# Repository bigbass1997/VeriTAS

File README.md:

### Description
VeriTAS is a combination of a replay device for performing Tool-Assisted-Speedruns (aka Tool-Assisted-Superruns) on physical hardware, and software tooling that interfaces with the device and assists in other TAS replay tasks.

The RP2040 microcontroller is the brains of this device. This project is still in development, and is a replacement/continuation of my previous device, the PICTAS. It is _not_ yet ready for wide-spread public use.

### Software Tooling
The [VeriTAS software](veritas-cli/) is a CLI tool that can perform various TAS replay related tasks, such as automated TAS dumping and video transcoding. It is also used for interfacing with the VeriTAS hardware.

### Input Displays
_Planned_

### Discord/Support
If you have questions or suggestions, you can find me on the [TASBot Labs](https://discord.tas.bot/) or [TASVideos](https://discord.gg/7KSr7eZVzG) Discord servers.

### Licensing
The `/veritas-hardware/` directory is licensed under CERN-OHL-W-V2, while all other files are dual licensed under MIT and APACHE 2.0.

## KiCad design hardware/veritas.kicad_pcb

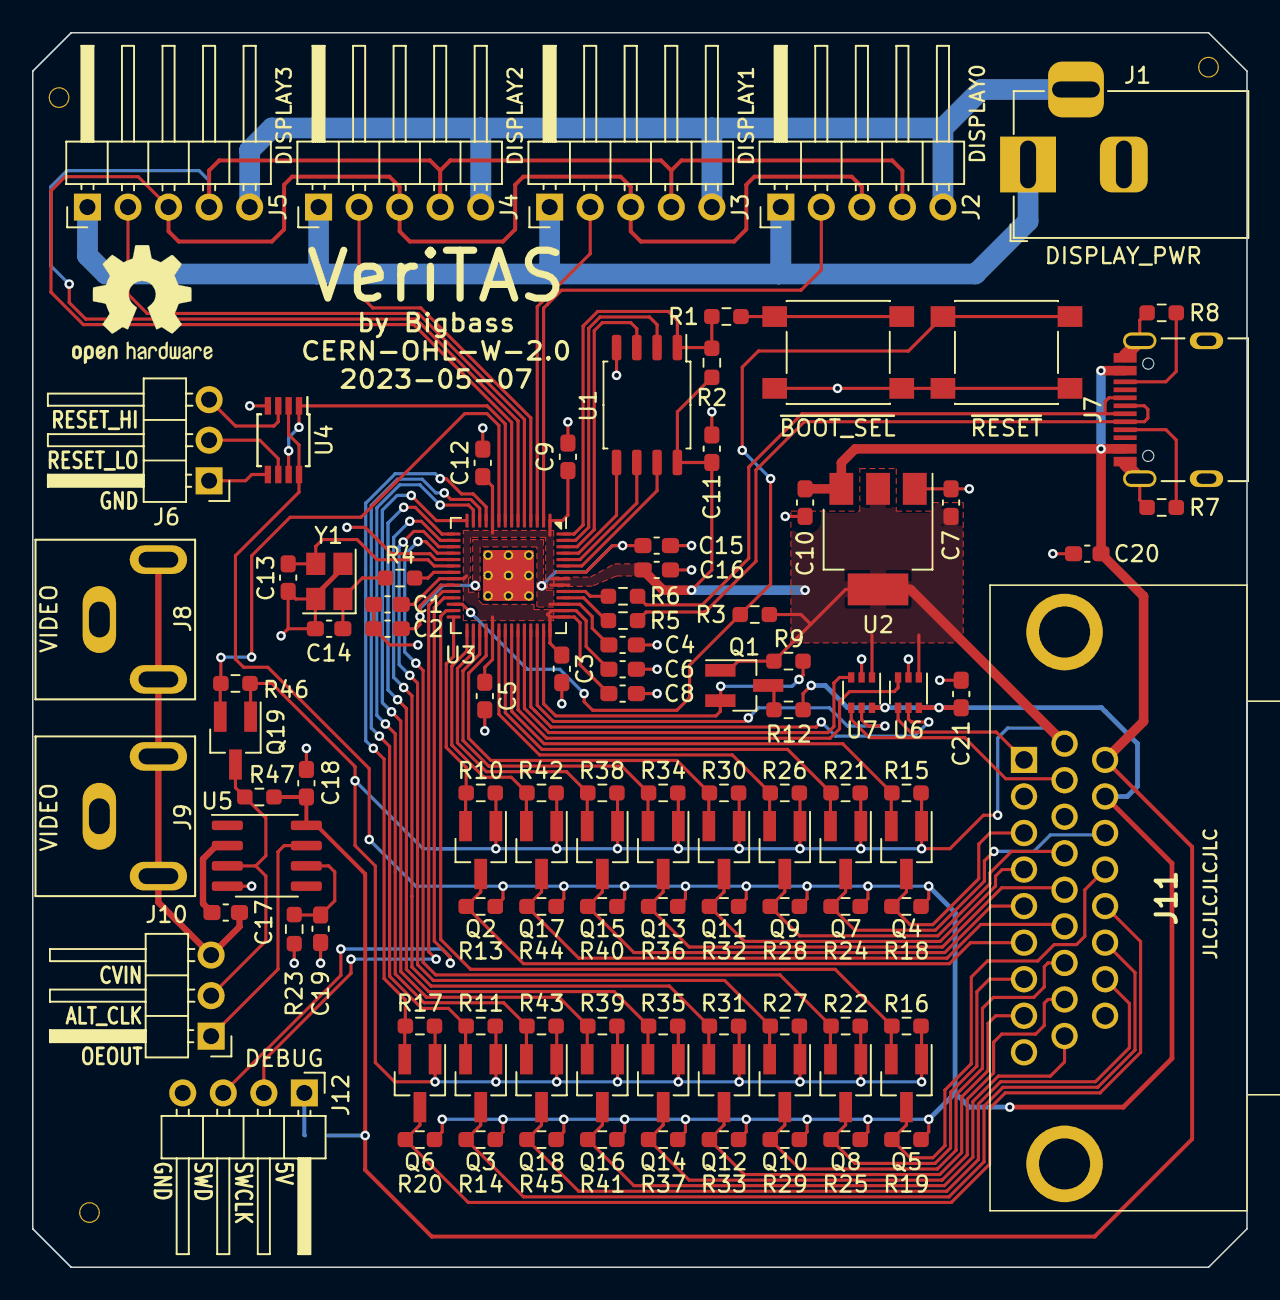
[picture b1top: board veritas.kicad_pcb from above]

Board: 2 copper layers, 76.1 x 77.3 mm, 110 parts (1 on the bottom side), 83 nets.

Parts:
C1, C2, C3, C4, C5, C6, C8, C9, C11, C12, C17, C18, C19, C20, C21: 0.1uF; C_0603_1608Metric_Pad1.08x0.95mm_HandSolder
C7, C10: 10uF; C_0603_1608Metric_Pad1.08x0.95mm_HandSolder
C13, C14: 27pF; C_0603_1608Metric_Pad1.08x0.95mm_HandSolder
C15, C16: 1uF; C_0603_1608Metric_Pad1.08x0.95mm_HandSolder
J1: DISPLAY_PWR; BarrelJack_Horizontal
J2: DISPLAY0; PinHeader_1x05_P2.54mm_Horizontal
J3: DISPLAY1; PinHeader_1x05_P2.54mm_Horizontal
J4: DISPLAY2; PinHeader_1x05_P2.54mm_Horizontal
J5: DISPLAY3; PinHeader_1x05_P2.54mm_Horizontal
J6: CON_RESET; PinHeader_1x03_P2.54mm_Horizontal
J7: USB2.0_C; TYPE-C-31-M-12
J8, J9: VIDEO; PJRAN1X1U04X
J10: SYNC; PinHeader_1x03_P2.54mm_Horizontal
J11: CONTROLLER_PORT; L77HDA26SD1CH4R
J12: DEBUG; PinHeader_1x04_P2.54mm_Horizontal
JP1: SolderJumper_2_Open; SolderJumper-2_P1.3mm_Open_TrianglePad1.0x1.5mm
Q1, Q2, Q3, Q4, Q5, Q6, Q7, Q8, Q9, Q10, Q11, Q12, Q13, Q14, Q15, Q16, Q17, Q18, Q19: 2N7002K; SOT-23_Handsoldering
R1, R4: 1K; R_0603_1608Metric_Pad0.98x0.95mm_HandSolder
R2, R3, R9, R10, R11, R12, R13, R14, R15, R16, R17, R18, R19, R20, R21, R22, R24, R25, R26, R27, R28, R29, R30, R31, R32, R33, R34, R35, R36, R37, R38, R39, R40, R41, R42, R43, R44, R45, R46, R47: 10K; R_0603_1608Metric_Pad0.98x0.95mm_HandSolder
R5, R6: 27; R_0603_1608Metric_Pad0.98x0.95mm_HandSolder
R7, R8: 5.1K; R_0603_1608Metric_Pad0.98x0.95mm_HandSolder
R23: 680K; R_0603_1608Metric_Pad0.98x0.95mm_HandSolder
SW1: ~{BOOT_SEL}; SW_SPST_PTS645
SW2: ~{RESET}; SW_SPST_PTS645
U1: W25Q128JVSIQ; SOIC-8_5.23x5.23mm_P1.27mm
U2: NCP1117ST33T3G; SOT-223-3_TabPin2
U3: RP2040
U4: 74LVC2G240; TSSOP-8_3x3mm_P0.65mm
U5: LM1881; SOIC-8_3.9x4.9mm_P1.27mm
U6, U7: SN74LVC1T45DRL; SOT-363_SC-70-6
Y1: 12MHz; Crystal_SMD_3225-4Pin_3.2x2.5mm

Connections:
+1V1: C2.1, C4.1, C15.2, U3.23 (DVDD), U3.45 (VREG_VOUT), U3.50 (DVDD)
+3V3: C1.1, C3.1, C5.1, C6.1, C7.1, C8.1, C9.1, C11.1, C12.1, C16.2, J11.10, Q1.1 (G), Q2.1 (G), Q3.1 (G), Q4.1 (G), Q5.1 (G), Q6.1 (G), Q7.1 (G), Q8.1 (G), Q9.1 (G), Q10.1 (G), Q11.1 (G), Q12.1 (G), Q13.1 (G), Q14.1 (G), Q15.1 (G), Q16.1 (G), Q17.1 (G), Q18.1 (G), Q19.1 (G), R2.2, R3.2, R9.2, R10.2, R11.2, R15.2, R16.2, R17.2, R21.2, R22.2, R26.2, R27.2, R30.2, R31.2, R34.2, R35.2, R38.2, R39.2, R42.2, R43.2, R46.2, U1.8 (VCC), U2.2 (VO), U3.1 (IOVDD), U3.10 (IOVDD), U3.22 (IOVDD), U3.33 (IOVDD), U3.42 (IOVDD), U3.43 (ADC_AVDD), U3.44 (VREG_IN), U3.48 (USB_VDD), U3.49 (IOVDD), U6.1 (VCCA), U7.1 (VCCA)
/CVIN: C17.2, J8.1 (In), J9.1 (In), J10.3
/D+: J7.A6 (D+), J7.B6 (D+), R6.2
/D-: J7.A7 (D-), J7.B7 (D-), R5.2
/LED_5V: J1.1, J2.1, J3.1, J4.1, J5.1
/RD+: R6.1, U3.47 (USB_DP)
/RD-: R5.1, U3.46 (USB_DM)
/RESET_HI: J6.3, U4.3 (2Y)
/RESET_LO: J6.2, U4.6 (1Y)
ALT_CLK_A: Q19.2 (S), R46.1, U3.9 (GPIO7)
ALT_CLK_B: J10.2, Q19.3 (D), R47.1, U5.3 (VSOUT)
CNT_0: Q6.2 (S), R17.1, U3.11 (GPIO8)
CNT_1: Q3.2 (S), R11.1, U3.12 (GPIO9)
CNT_2: Q18.2 (S), R43.1, U3.13 (GPIO10)
CNT_3: Q16.2 (S), R39.1, U3.14 (GPIO11)
CNT_4: Q14.2 (S), R35.1, U3.15 (GPIO12)
CNT_5: Q12.2 (S), R31.1, U3.16 (GPIO13)
CNT_6: Q10.2 (S), R27.1, U3.17 (GPIO14)
CNT_7: Q8.2 (S), R22.1, U3.18 (GPIO15)
CNT_8: Q5.2 (S), R16.1, U3.27 (GPIO16)
CNT_9: Q2.2 (S), R10.1, U3.28 (GPIO17)
CNT_10: Q17.2 (S), R42.1, U3.29 (GPIO18)
CNT_11: Q15.2 (S), R38.1, U3.30 (GPIO19)
CNT_12: Q13.2 (S), R34.1, U3.31 (GPIO20)
CNT_13: Q11.2 (S), R30.1, U3.32 (GPIO21)
CNT_14: Q9.2 (S), R26.1, U3.34 (GPIO22)
CNT_15: Q7.2 (S), R21.1, U3.35 (GPIO23)
CNT_16: Q4.2 (S), R15.1, U3.36 (GPIO24)
CNT_17: U3.37 (GPIO25), U6.3 (A)
CNT_17_DIR: U3.39 (GPIO27_ADC1), U6.5 (DIR)
CNT_18: U3.38 (GPIO26_ADC0), U7.3 (A)
CNT_18_DIR: U3.40 (GPIO28_ADC2), U7.5 (DIR)
CP_1: J11.1, U6.4 (B)
CP_3: J11.3, Q4.3 (D), R18.1
CP_4: J11.4, Q11.3 (D), R32.1
CP_5: J11.5, Q15.3 (D), R40.1
CP_6: J11.6, Q2.3 (D), R13.1
CP_7: J11.7, Q8.3 (D), R25.1
CP_8: J11.8, Q12.3 (D), R33.1
CP_11: J11.11, U7.4 (B)
CP_13: J11.13, Q9.3 (D), R28.1
CP_14: J11.14, Q13.3 (D), R36.1
CP_15: J11.15, Q17.3 (D), R44.1
CP_16: J11.16, Q10.3 (D), R29.1
CP_17: J11.17, Q14.3 (D), R37.1
CP_18: J11.18, Q16.3 (D), R41.1
CP_21: J11.21, Q7.3 (D), R24.1
CP_22: J11.22, Q5.3 (D), R19.1
CP_23: J11.23, Q6.3 (D), R20.1
CP_24: J11.24, Q3.3 (D), R14.1
CP_25: J11.25, Q18.3 (D), R45.1
DETECT: Q1.2 (S), R9.1, U3.41 (GPIO29_ADC3)
DISPLAY_CLK: J2.3, J3.3, J4.3, J5.3, U3.7 (GPIO5)
DISPLAY_SER: J2.4, J3.4, J4.4, J5.4, U3.6 (GPIO4)
DISPLAY_STROBE0: J2.2, U3.2 (GPIO0)
DISPLAY_STROBE1: J3.2, U3.3 (GPIO1)
DISPLAY_STROBE2: J4.2, U3.4 (GPIO2)
DISPLAY_STROBE3: J5.2, U3.5 (GPIO3)
GND: C1.2, C2.2, C3.2, C4.2, C5.2, C6.2, C7.2, C8.2, C9.2, C10.2, C11.2, C12.2, C13.1, C14.1, C15.1, C16.1, C18.1, C19.1, C20.2, C21.2, J1.2, J1.3, J2.5, J3.5, J4.5, J5.5, J6.1, J7.A1 (GND), J7.A12 (GND), J7.B1 (GND), J7.B12 (GND), J7.S1 (SHIELD), J8.2 (Ext), J9.2 (Ext), J11.0, J11.9, J11.26, J12.4, R7.1, R8.1, R23.2, SW1.1, SW2.1, U1.4 (GND), U2.1 (GND), U3.19 (TESTEN), U3.57 (GND), U4.4 (GND), U4.5 (2A), U5.4 (GND), U6.2 (GND), U7.2 (GND), Y1.2, Y1.4
unnamed: C14.2, R4.1, Y1.1
unnamed: J7.A5 (CC1), R7.2
unnamed: J7.B5 (CC2), R8.2
unnamed: J12.1, JP1.2 (B)
unnamed: Q1.3 (D), R12.1
unnamed: R1.1, SW1.2
unnamed: R3.1, SW2.2, U3.26 (RUN)
unnamed: C13.2, U3.20 (XIN), Y1.3
unnamed: R4.2, U3.21 (XOUT)
unnamed: C17.1, U5.2 (CVIN)
unnamed: C19.2, R23.1, U5.6 (RSET)
OEOUT: J10.1, U5.7 (OEOUT)
QSPI_CLK: U1.6 (CLK), U3.52 (QSPI_SCLK)
QSPI_IO0: U1.5 (DI(IO0)), U3.53 (QSPI_SD0)
QSPI_IO1: U1.2 (DO(IO1)), U3.55 (QSPI_SD1)
QSPI_IO2: U1.3 (IO2), U3.54 (QSPI_SD2)
QSPI_IO3: U1.7 (IO3), U3.51 (QSPI_SD3)
SWCLK: J12.2, U3.24 (SWCLK)
SWD: J12.3, U3.25 (SWD)
SYSTEM_PWR: C21.1, J11.20, R12.2, R13.2, R14.2, R18.2, R19.2, R20.2, R24.2, R25.2, R28.2, R29.2, R32.2, R33.2, R36.2, R37.2, R40.2, R41.2, R44.2, R45.2, U4.2 (1A), U4.8 (VCC), U6.6 (VCCB), U7.6 (VCCB)
VBUS: C10.1, C18.2, C20.1, J7.A4 (VBUS), J7.A9 (VBUS), J7.B4 (VBUS), J7.B9 (VBUS), J11.19, JP1.1 (A), R47.2, U2.3 (VI), U5.8 (VCC)
~CON_RESET: U3.8 (GPIO6), U4.1 (1~OE), U4.7 (2~OE)
~QSPI_CS: R1.2, R2.1, U1.1 (~CS), U3.56 (QSPI_SS)

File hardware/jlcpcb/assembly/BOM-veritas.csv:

Comment,Designator,Footprint,LCSC
27pF,"C13,C14",C_0603_1608Metric_Pad1.08x0.95mm_HandSolder,C107045
LMBT3946DW1T1G,Q1,SOT-363_SC-70-6_Handsoldering,C136169
0.1uF,"C1,C11,C12,C17,C18,C19,C2,C20,C21,C3,C4,C5,C6,C8,C9",C_0603_1608Metric_Pad1.08x0.95mm_HandSolder,C14663
1uF,"C15,C16",C_0603_1608Metric_Pad1.08x0.95mm_HandSolder,C15849
USB2.0_C,J7,TYPE-C-31-M-12,C165948
RP2040,U3,RP2040,C2040
1K,"R1,R3",R_0603_1608Metric_Pad0.98x0.95mm_HandSolder,C21190
~{BOOT_SEL},SW1,SW_SPST_PTS645,C221875
5.1K,"R6,R7",R_0603_1608Metric_Pad0.98x0.95mm_HandSolder,C23186
27,"R4,R5",R_0603_1608Metric_Pad0.98x0.95mm_HandSolder,C25190
10K,"R10,R11,R12,R13,R14,R15,R16,R17,R18,R19,R2,R20,R21,R23,R24,R25,R26,R27,R28,R29,R30,R31,R32,R33,R34,R35,R36,R37,R38,R39,R40,R41,R42,R43,R44,R45,R46,R8,R9",R_0603_1608Metric_Pad0.98x0.95mm_HandSolder,C25804
680K,R22,R_0603_1608Metric_Pad0.98x0.95mm_HandSolder,C25822
NCP1117ST33T3G,U2,SOT-223-3_TabPin2,C26537
12MHz,Y1,Crystal_SMD_HC49-SD,C326543
2N7002K,"Q10,Q11,Q12,Q13,Q14,Q15,Q16,Q17,Q18,Q19,Q2,Q20,Q3,Q4,Q5,Q6,Q7,Q8,Q9",SOT-23_Handsoldering,C8545
SN74LVC1T45DRL,"U5,U6",SOT-563,C9382
10uF,"C10,C7",C_0603_1608Metric_Pad1.08x0.95mm_HandSolder,C96446
W25Q128JVSIQ,U1,SOIC-8_5.23x5.23mm_P1.27mm,C97521
DISPLAY3,J5,PinHeader_1x05_P2.54mm_Horizontal,
SYNC,J10,PinHeader_1x03_P2.54mm_Horizontal,
VIDEO,J9,PJRAN1X1U04X,
DISPLAY0,J2,PinHeader_1x05_P2.54mm_Horizontal,
DEBUG,J12,PinHeader_1x04_P2.54mm_Horizontal,
VIDEO,J8,PJRAN1X1U04X,
LM1881,U4,SOIC-8_3.9x4.9mm_P1.27mm,
DISPLAY2,J4,PinHeader_1x05_P2.54mm_Horizontal,
CON_RESET,J6,PinHeader_1x03_P2.54mm_Horizontal,
DISPLAY1,J3,PinHeader_1x05_P2.54mm_Horizontal,
DISPLAY_PWR,J1,BarrelJack_Horizontal,
CONTROLLER_PORT,J11,L77HDA26SD1CH4R,

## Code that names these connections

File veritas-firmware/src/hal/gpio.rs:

#![allow(unused)]

use rp2040_pac::{IO_BANK0, PADS_BANK0, SIO};
use rp2040_pac::io_bank0::gpio::gpio_ctrl::{FUNCSEL_A, FUNCSEL_R};
use rp2040_pac::pads_bank0::gpio::{DRIVE_A, DRIVE_R};

pub const PIN_DISPLAY_STROBE0: Gpio = Gpio(0);
pub const PIN_DISPLAY_STROBE1: Gpio = Gpio(1);
pub const PIN_DISPLAY_STROBE2: Gpio = Gpio(2);
pub const PIN_DISPLAY_STROBE3: Gpio = Gpio(3);
pub const PIN_DISPLAY_SER: Gpio = Gpio(4);
pub const PIN_DISPLAY_CLK: Gpio = Gpio(5);

pub const PIN_CON_RESET: Gpio = Gpio(6);
pub const PIN_ALT_CLK: Gpio = Gpio(7);

pub const PIN_CNT_0: Gpio = Gpio(8);
pub const PIN_CNT_1: Gpio = Gpio(9);
pub const PIN_CNT_2: Gpio = Gpio(10);
pub const PIN_CNT_3: Gpio = Gpio(11);
pub const PIN_CNT_4: Gpio = Gpio(12);
pub const PIN_CNT_5: Gpio = Gpio(13);
pub const PIN_CNT_6: Gpio = Gpio(14);
pub const PIN_CNT_7: Gpio = Gpio(15);
pub const PIN_CNT_8: Gpio = Gpio(16);
pub const PIN_CNT_9: Gpio = Gpio(17);
pub const PIN_CNT_10: Gpio = Gpio(18);
pub const PIN_CNT_11: Gpio = Gpio(19);
pub const PIN_CNT_12: Gpio = Gpio(20);
pub const PIN_CNT_13: Gpio = Gpio(21);
pub const PIN_CNT_14: Gpio = Gpio(22);
pub const PIN_CNT_15: Gpio = Gpio(23);
pub const PIN_CNT_16: Gpio = Gpio(24);

pub const PIN_CNT_17: Gpio = Gpio(25);
pub const PIN_CNT_18: Gpio = Gpio(26);
pub const PIN_CNT_17_DIR: Gpio = Gpio(27);
pub const PIN_CNT_18_DIR: Gpio = Gpio(28);

pub const PIN_DETECT: Gpio = Gpio(29);

pub const CP_1: Gpio = PIN_CNT_17;
pub const CP_1_DIR: Gpio = PIN_CNT_17_DIR;

//pub const CP_2: Gpio = PIN_CNT_; // Unconnected
pub const CP_3: Gpio = PIN_CNT_16;
pub const CP_4: Gpio = PIN_CNT_13;
pub const CP_5: Gpio = PIN_CNT_11;
pub const CP_6: Gpio = PIN_CNT_9;
pub const CP_7: Gpio = PIN_CNT_7;
pub const CP_8: Gpio = PIN_CNT_5;

pub const CP_11: Gpio = PIN_CNT_18;
pub const CP_11_DIR: Gpio = PIN_CNT_18_DIR;

//pub const CP_12: Gpio = PIN_CNT_; // Unconnected
pub const CP_13: Gpio = PIN_CNT_14;
pub const CP_14: Gpio = PIN_CNT_12;
pub const CP_15: Gpio = PIN_CNT_10;
pub const CP_16: Gpio = PIN_CNT_6;
pub const CP_17: Gpio = PIN_CNT_4;
pub const CP_18: Gpio = PIN_CNT_3;

pub const CP_21: Gpio = PIN_CNT_15;
pub const CP_22: Gpio = PIN_CNT_8;
pub const CP_23: Gpio = PIN_CNT_0;
pub const CP_24: Gpio = PIN_CNT_1;
pub const CP_25: Gpio = PIN_CNT_2;

#[derive(Debug, Clone, Copy, PartialEq, Eq)]
pub struct Gpio(pub usize);
impl Gpio {
    pub const fn new(gpio: usize) -> Self {
        Self(gpio)
    }
    
    #[inline(always)]
    pub fn function(self) -> FUNCSEL_R {
        unsafe { (*IO_BANK0::ptr()).gpio(self.0).gpio_ctrl().read().funcsel() }
    }
    
    #[inline(always)]
    pub fn set_function(self, func: FUNCSEL_A) -> Self {
        unsafe {
            (*IO_BANK0::ptr()).gpio(self.0).gpio_ctrl().write_with_zero(|w| w.funcsel().variant(func));
            self.set_output_disable(false);
        }
        
        self
    }
    
    #[inline(always)]
    pub fn output_disable(self) -> bool {
        unsafe { (*PADS_BANK0::ptr()).gpio(self.0).read().od().bit() }
    }
    
    #[inline(always)]
    pub fn set_output_disable(self, od: bool) -> Self {
        unsafe { (*PADS_BANK0::ptr()).gpio(self.0).modify(|_, w| w.od().bit(od)); }
        
        self
    }
    
    #[inline(always)]
    pub fn input_enable(self) -> bool {
        unsafe {
            (*PADS_BANK0::ptr()).gpio(self.0).read().ie().bit()
        }
    }
    
    #[inline(always)]
    pub fn set_input_enable(self, ie: bool) -> Self {
        unsafe { (*PADS_BANK0::ptr()).gpio(self.0).modify(|_, w| w.ie().bit(ie)); }
        
        self
    }
    
    /// Returns the state of this GPIO's SIO output enable.
    /// 
    /// Note: This setting should have no effect if the GPIO's function is _not_ set to SIO. 
    #[inline(always)]
    pub fn output_enable(self) -> bool {
        unsafe {
            (*SIO::ptr()).gpio_oe().read().bits() & (1 << self.0) != 0
        }
    }
    
    /// Configures this GPIO's SIO output enable.
    /// 
    /// Note: This setting should have no effect if the GPIO's function is _not_ set to SIO. 
    #[inline(always)]
    pub fn set_sio_output_enable(self, oe: bool) -> Self {
        unsafe {
            if oe {
                (*SIO::ptr()).gpio_oe_set().write(|w| w.bits(1 << self.0));
            } else {
                (*SIO::ptr()).gpio_oe_clr().write(|w| w.bits(1 << self.0));
            }
        }
        
        self
    }
    
    #[inline(always)]
    pub fn drive(self) -> DRIVE_R {
        unsafe { (*PADS_BANK0::ptr()).gpio(self.0).read().drive() }
    }
    
    #[inline(always)]
    pub fn set_drive(self, drive: DRIVE_A) -> Self {
        unsafe { (*PADS_BANK0::ptr()).gpio(self.0).modify(|_, w| w.drive().variant(drive)); }
        
        self
    }
    
    #[inline(always)]
    pub fn pull_up_enable(self) -> bool {
        unsafe { (*PADS_BANK0::ptr()).gpio(self.0).read().pue().bit() }
    }
    
    #[inline(always)]
    pub fn set_pull_up_enable(self, pue: bool) -> Self {
        unsafe { (*PADS_BANK0::ptr()).gpio(self.0).modify(|_, w| w.pue().bit(pue)); }
        
        self
    }
    
    #[inline(always)]
    pub fn pull_down_enable(self) -> bool {
        unsafe { (*PADS_BANK0::ptr()).gpio(self.0).read().pde().bit() }
    }
    
    #[inline(always)]
    pub fn set_pull_down_enable(self, pde: bool) -> Self {
        unsafe { (*PADS_BANK0::ptr()).gpio(self.0).modify(|_, w| w.pde().bit(pde)); }
        
        self
    }
    
    #[inline(always)]
    pub fn schmitt_enable(self) -> bool {
        unsafe { (*PADS_BANK0::ptr()).gpio(self.0).read().schmitt().bit() }
    }
    
    #[inline(always)]
    pub fn set_schmitt_enable(self, schmitt: bool) -> Self {
        unsafe { (*PADS_BANK0::ptr()).gpio(self.0).modify(|_, w| w.schmitt().bit(schmitt)); }
        
        self
    }
    
    #[inline(always)]
    pub fn slewrate(self) -> bool {
        unsafe { (*PADS_BANK0::ptr()).gpio(self.0).read().slewfast().bit() }
    }
    
    #[inline(always)]
    pub fn set_slewrate(self, is_fast: bool) -> Self {
        unsafe { (*PADS_BANK0::ptr()).gpio(self.0).modify(|_, w| w.slewfast().bit(is_fast)); }
        
        self
    }
    
    #[inline(always)]
    pub fn is_high(self) -> bool {
        unsafe {
            (*SIO::ptr()).gpio_in().read().bits() & (1 << self.0) != 0
        }
    }
    
    #[inline(always)]
    pub fn is_low(self) -> bool {
        unsafe {
            (*SIO::ptr()).gpio_in().read().bits() & (1 << self.0) == 0
        }
    }
    
    #[inline(always)]
    pub fn set_high(self) -> Self {
        unsafe {
            (*SIO::ptr()).gpio_out_set().write(|w| w.bits(1 << self.0));
        }
        
        self
    }
    
    #[inline(always)]
    pub fn set_low(self) -> Self {
        unsafe {
            (*SIO::ptr()).gpio_out_clr().write(|w| w.bits(1 << self.0));
        }
        
        self
    }
    
    #[inline(always)]
    pub fn into_input(self, pull_up: bool, pull_down: bool) -> Self {
        self.set_function(FUNCSEL_A::SIO);
        self.set_pull_down_enable(pull_down);
        self.set_pull_up_enable(pull_up);
        self.set_output_disable(true);
        self.set_input_enable(true);
        self.set_sio_output_enable(false);
        
        self
    }
    
    #[inline(always)]
    pub fn into_output(self, pull_up: bool, pull_down: bool) -> Self {
        self.set_function(FUNCSEL_A::SIO);
        self.set_pull_down_enable(pull_down);
        self.set_pull_up_enable(pull_up);
        self.set_output_disable(false);
        self.set_input_enable(false);
        self.set_sio_output_enable(true);
        
        self
    }
}

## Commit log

2022-07-16 Initial commit.
2022-07-17 Reworked dumping data into well-defined structs. Still need logic for movies to fetch their expected rom hash.
2022-07-18 Implemented rom searching and interfacing with FCEUX. Bizhawk is next..
2022-07-19 Added warnings for unsupported movie formats and for invalid Pub/Sub IDs.
2022-07-19 Implemented Bizhawk interfacing.
2022-07-20 Fixed clap bug for encode command.
2022-07-20 Added dump file location to log output.
2022-08-08 Partially migrate away from using the restrictive RP2040-HAL, and more toward a custom HAL using the RP2040-PAC.
2022-08-09 Implemented basic N64 replay functionality (temporary host API), and GPIO functions.
2022-08-10 Cleaned and reorganized code some.
2022-08-11 Added global allocator, and started on storing auxiliary data storage (e.g. transitions).
2022-08-11 Migrate software into project tree.
2022-08-11 Remove duplicated files caused by history merge.
2022-08-11 Updated READMEs and added license notice.
2022-08-12 Fixed significant issues with custom GPIO functions, and started on NES replay.
2022-08-12 Stop using board-specific rp-pico dependency. Fix imports accordingly.
2022-08-12 Setup separate, mutable, Interrupt Vector Tables for each core.
2022-08-12 Hopefully fixed remaining GPIO issues.
2022-08-12 1-player NES replay is functional.
2022-08-14 Implemented 2-player NES replay.
2022-08-24 Finished first hardware prototype.
2022-08-26 Ignore ibom.
2022-08-27 Started organizing host<->device communication protocol.
2022-08-27 Added partial protocol documentation to README.
2022-08-27 Update lua scripts to use latest dev version of TASD spec.
2022-08-27 Implemented structured replay device communication protocol.
2022-08-27 Included system byte in ProvideInput command response.
2022-08-27 Fixed TASD API bug, and added transition debug messages to Bizhawk script.
2022-09-06 Improved ProvideInput communication and added manual control for NES.
2022-09-06 Changed from UART to USB communication. Changed NES pinout for testing. Added gpio pin consts which reflect PCB pinout.
2022-09-06 Completed new PCB revision. Includes different voltage translation and removal of unnecessary parts.
2022-09-11 Changed file lookup to use Walkdir, and updated dependencies.
2022-09-11 Added stale cache detection, and added command to force refresh.
2022-09-11 Added optional rom override for local movies. Added FDS system detection.
2022-09-13 Added dump support for TASVideos userfiles.
2022-09-19 Updated GPIO pinout and fixed input misalignment bugs.
2022-09-19 Partially implemented transition support. Host communication is missing.
2022-10-22 Changed tasvideos-api-rs dependency to use crates.io instead of local path.
2023-01-13 Possible fix for resets in dumps.
2023-03-30 Don't know how up to date this is, but pushing it anyways. Will push updated gerbers in next PCB revision.
2023-03-30 Updated KiCad to v7.0
2023-03-30 Removed debug junk from release profile, fixing inconsistent execution timing.
2023-03-30 Added workaround reset functionality by using directional bus transceiver. Added limited transition handling (currently disabled).
2023-03-30 All local changes have been pushed at this point. Device confirmed working with Wizards & Warriors III, and Rush'n Attack.
2023-03-31 Updated RP2040-HAL, fixing USB bug where first communication attempt times-out. Discovered bug in BizHawk dump script (NOT fixed, just added a workaround), where the transition index is double what i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
2023-03-31 Cleaning up some warnings.
2023-04-01 Fixed defmt getting stuck randomly after reprogramming.
2023-04-01 Added input displays and changed NES latch handling.
2023-04-07 Updated dependencies and changed to clap's derive parser.
2023-04-11 Rewrote USB handling to use bincode, instead of manual decoding/encoding bytes. Finally fixed long-standing bug that caused seemingly random delays (caused by XIP cache misses; worsened by using binc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
2023-04-12 Fixed device status response.
2023-04-12 Removed unneeded comments and debug code.
2023-04-12 Fixed unintended interrupt triggers when starting a replay. Also no longer necessary to prepend the input stream with a blank frame of data.
2023-04-13 Fixed potential alarm softlock after exiting ReplayNes mode.
2023-04-13 Added RAM initialization for marked functions.
2023-04-14 Fixed minor usability bugs.
2023-04-14 Finished implementing reset transitions (verified working with Alwa's Awakening).
2023-04-14 Added option to disable the initial reset, for rare cases where a reset may disrupt the initial state of a game.
2023-04-27 Fixed missing symbol library from repo.
2023-04-27 Added 3-button Genesis support. Moved REPLAY_STATE to the replay core, doesn't need to be console-specific. Added interrupt helper functions. --manual argument now takes a string to specify the desir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
2023-06-12 Produced new version as of 2023-05-07: - Replaced reset circuit with TTL-compatible buffer IC (untested; uses /OE to isolate signal from console until reset is activated) - Set more components to be 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
2023-06-12 Fixed local override argument being ignored
2023-06-12 Added input display support for genesis controllers (includes temporary patch for incorrectly designed bit order)
2023-06-12 Added dump and replay support for TAS movies made with Gens.
2023-06-14 Added support for fetching local movies when dumping.
2023-09-12 Overhauled dumping code. Switched to using UTF8 paths from camino.
2025-08-18 All changes since starting revamp; too many to list.
2025-08-18 Update rust edition to 2024
2025-08-18 Updated crates to latest versions.
2025-08-19 Revamped GPIO and interrupts.
2025-09-12 Added movie dumping for FCEUX and (NES) BizHawk, with more robust emulator selection. Updated README and added/changed software licenses to MIT/APACHE2.0.
2025-09-12 Added ability to report NES controller read period (debug console only for now). Changed NES overread default to match a real controller.
2025-09-12 Fixed license symlinks.
2025-09-12 Fixed README links.
2025-09-12 Fix BizHawk version parsing and disable fallback to first in list.
2025-09-17 Added latch filter auto-detection feature. Moved display updating to CPU (previously this code could've caused unexpected cache misses during time-critical moments.)
2025-09-17 Added dump config for emulator list and added CLI arg for easily registering new emulators.
2025-09-17 Added support for parsing FM2s with non-UTF8 ROM filenames.
2025-09-18 Protect against missing emu.exit() function in FCEUX pre-v2.2.0.
2025-09-18 Update tasvideos-api-rs (and other dependencies).
2025-09-19 Do not assume userfiles are always compressed.
2025-09-27 Added additional methods for specifying a userfile ID.
2025-11-23 Fix unexpected state when <2 bytes of input data are sent to device.
2025-11-23 Remove unused code and update dependencies.
2025-11-23 Hopefully future-proof bizhawk bit library compatibility. Fixed and added missing NES latch filter.
2025-11-23 Added rudimentary Everdrive N8 menu simulation and automation. Added minimal replay device communication.
2025-11-23 Removed hardcoded path (Note: N8 menu navigation is still experimental at this stage)

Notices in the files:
README.md:
License: CERN
License: MIT
License: APACHE2.0
hardware/veritas.kicad_pcb:
CERN-OHL-W-2.0
